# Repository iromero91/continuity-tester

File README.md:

# Low Power Continuity Tester

These are the hardware and software design files for my square inch
contest entry, the low power continuity tester.

## Goals

The design goals for this project are the following:

* **Small size**: maximum of 1 square inch PCB area.

* **Low power**: Should run for a decent amount on time on a single
  CR2032 cell.

* **Fully featured**: Have at least:

  * *Low voltage continuity test mode*: Compliance voltage < 0.5v, low
    current.

  * *Inverse continuity mode*: Beep if continuity is broken.

  * *Both modes with "latching" glitch capture*: start beeping
    immediately and keep beeping for at least a split second.

  * *Diode test mode*: Short beep on forward voltage within diode drop
    (0.1-0.7v), continuous beep on short circuit.

* **Simple to use**: no power switch, turn on by touching probes, mode
  switch with a single button.

* **Low cost!**

## Implementation

To achieve all those goals I decided to base my implementation around
a microcontroller, namely the PIC12LF1571, which is a stunningly cheap
and feature packed device. Digikey has it for
[50 cents a piece][PIC12LF1571-I/SN-ND] at quantity 10! that's barely
17 cents more than what you'd pay for a humble [555][LM555CMFS-ND]!
For your 50 cents you get quite a spread of peripherals: a fixed
voltage reference, a 10 bit adc, a 5 bit DAC(!), 3 16-bit PWMs (!!),
the standard 3 timers on top of that, analog comparator, 3.5k of flash
and 256 bytes of SRAM. Truly remarkable.

Another remarkable thing about this chip which makes it suitable to
achieve my goals is that it can be made to operate under very low
voltages (down to 1.8v) and using very little power. As low as a few
hundred nanowatts (that's less than a millionth of a watt) while
sleeping, allowing standby times measured in years.

### Electronics

The analog part of the circuit is extremely simplistic, just 3
resistors. The design is inspired on [elm-chan's][elms-tester] tester,
but with an aditional IO pin on the negative side of the resistor
divider. This extra pin provides aditional control for the diode test
feature and allows the tester to be turned on by touching probes.

The simplicity of the circuit is also it's Achiles Heel, it doesn't
provide any input protection at all, relying instead on the built in
protection diodes of the microcontroller. The reason why I didn't
include any input protection is because I couldn't find any protection
scheme that would afford enough protection without compromising power
consumption or precision. For example, using a simple 3.3v zener diode
on the input would leak an appreciable amount of current at 3V, so
much in fact that the diode itself would consume more power than the
pic does while asleep! *This circuit should never be used on circuits
under power, and certainly NOT anywhere near any mains/line power
cables!!!*

### Firmware

The firmware is written in C, using Microchip's MPLAB X and XC8
compiler in free mode. The code is configured as a simple state
machine:

The CPU runs at the slowest internal oscillator speed (31kHz) to save
power. On reset it jumps straight into sleep mode, where it lays
dormant until a button press is detected or the leads are touched
together. That is achieved by setting up an interrupt on pin change
right before going to sleep, the interrupt hardware still works
without a clock, which allows the processor to still be useful while
only using less than a microwatt of power.

Once it's woken up, the microcontroller enters a loop where it
continuously samples the ADC, detecting wether the resistance in
between the probes is low enough to signal continuity or not. The ADC
module and voltage references are turned on and off as necessary to
use as little power as possible. While in this mode I've measured an
average current consumption of around 150 to 200 microamps, which
would allow the tester to have over 800 hours of battery life.

Each idle state blinks the led to signal which mode the tester is in,
for continuity it's a single blink followed by a long pause, for
inverse continuity it's 2, and for diodes it's 3 fast blinks followed
by a long pause. The user can switch modes by pressing the button.

When the condition of continuity (or discontinuity) is detected, the
beeper is turned on, using one of the PWM channels to output a square
wave into the piezo buzzer. Once there is no more continuity (or
discontinuity), a count is started so that any "glitch" is stretched
to at least a split second, making it easier to hear sporadic
contacts.

The diode tester is slightly different, the beeper is started as soon
as the voltage in the tips is below 0.7V (a typical silicon diode
drop), and will stop a split second later if that voltage stays above
0.1V (just below what would drop on a shottky diode). If it's any
longer, the beeper will stay on indefinitely. This mode makes it easy
to test diodes for opens and shorts since a normal diode would produce
a short beep, a shorted diode would produce a continuous beep, and an
open one wouldn't beep at all.

## Bill of materials

* Main chip: U1, [Microchip PIC12LF1571][PIC12LF1571-I/SN-ND] ($0.50 @ qty 10)
* Buzzer: SP1, [Murata PKM13EPYH4000-A0][490-4698-ND] ($0.49 @ qty 10)
* Battery Holder: BT1, [Linx BAT-HLD-001-THM][BAT-HLD-001-THM-ND] ($0.28 @ qty 10)
* Button: SW1, [TE Connectivity 1825910-7][450-1804-ND] ($0.06 @ qty 10)
* Decoupling cap: C1, 100nF, 0603, ceramic. (~$0.02)
* Resistors: R1, R5, 4k7; R2, R3, R4, 22k; 0805 resistors (~$0.05)
* PCB: OSHPark 3 1x1 inch boards for $5 ($1.66 ea)
 
**Total bom cost for a prototype run**: $3.06 each! (more than half of it is the prototype PCB)

## License

Copyright 2015 Jose I. Romero.

The schematic, PCB and firmware are free software, released under the
GNU GPL as published by the Free Software Foundation, version 3. See
LICENSE.txt for more details.

[PIC12LF1571-I/SN-ND]: http://www.digikey.com/product-detail/en/PIC12LF1571-I%2FSN/PIC12LF1571-I%2FSN-ND/4739318
[LM555CMFS-ND]: http://www.digikey.com/product-detail/en/LM555CM/LM555CMFS-ND/1051271
[elms-tester]: http://elm-chan.org/works/cch/report_e.html
[490-4698-ND]: http://www.digikey.com/product-detail/en/PKM13EPYH4000-A0/490-4698-ND/1219329
[BAT-HLD-001-THM-ND]: http://www.digikey.com/product-detail/en/BAT-HLD-001-THM/BAT-HLD-001-THM-ND/3044009

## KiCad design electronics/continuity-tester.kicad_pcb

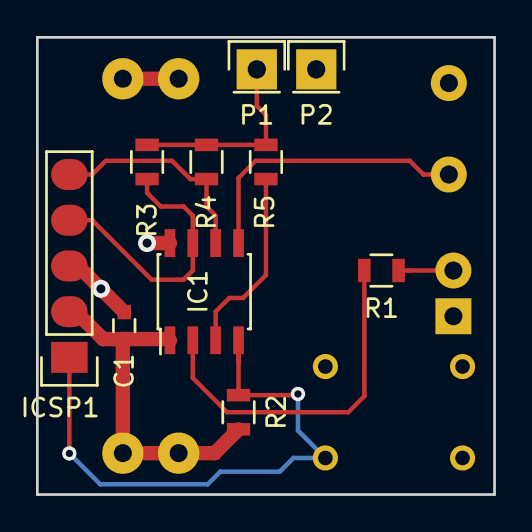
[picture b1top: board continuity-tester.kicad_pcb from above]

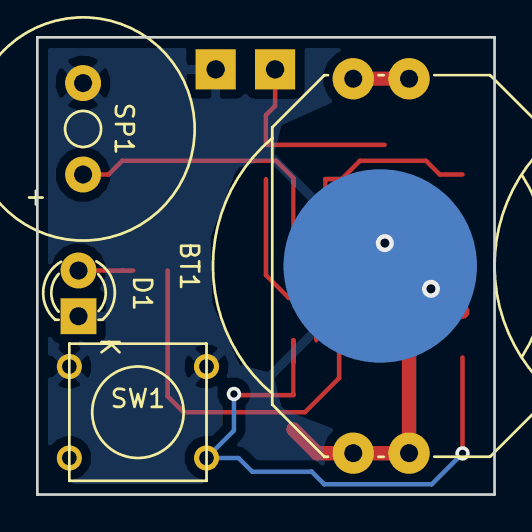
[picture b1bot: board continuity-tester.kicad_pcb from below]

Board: 2 copper layers, 25.4 x 25.4 mm, 14 parts (4 on the bottom side), 10 nets.

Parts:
BT1: CR2032; BAT-HLD-001-THM-OTL
C1: 100n; C_0603
D1: LED; LED-3MM
IC1: PIC12LF1571-I/SN; SOIC-8_3.9x4.9mm_Pitch1.27mm
ICSP1: CONN_01X05; Pin_Header_Straight_1x05
P1, P2: CONN_01X01; Pin_Header_Straight_1x01
R1: 4K7; R_0805
R2, R3, R4: 22k; R_0805
R5: 4k7; R_0805
SP1: SPEAKER; Buzzer_12x9.5RM7.6
SW1: SW_PUSH; SW_PUSH_SMALL

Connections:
unnamed: BT1.1, C1.1, IC1.1, ICSP1.2, R2.2
unnamed: BT1.2, C1.2, D1.1, IC1.8, ICSP1.3, P2.1, SP1.2, SW1.1
unnamed: D1.2, R1.1
unnamed: IC1.2, R1.2
unnamed: IC1.3, R5.2
unnamed: IC1.4, ICSP1.1, R2.1, SW1.2
unnamed: IC1.5, SP1.1
unnamed: IC1.6, ICSP1.5, R4.2
unnamed: IC1.7, ICSP1.4, R3.2
unnamed: P1.1, R3.1, R4.1, R5.1

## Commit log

2015-11-19 Initial revision
2015-11-20 Finalized first version of firmware, GPLv3 license.
2015-11-20 Timing analysis and optimization, sampling at ~50Hz
2015-11-21 Switched to PICkit3 for development
2015-11-21 Added battery holders library
2015-11-22 First revision of the PCB
2015-11-22 Ported firmware to the PIC12LF1571
2015-11-23 Improved ADC defines and use of fixed voltage reference.
2015-11-23 Fix error in .gitignore, was not ignoring PCB backup files
2015-11-25 New PCB revision, sent to fab.
2015-11-27 Added README file, getting ready for github
